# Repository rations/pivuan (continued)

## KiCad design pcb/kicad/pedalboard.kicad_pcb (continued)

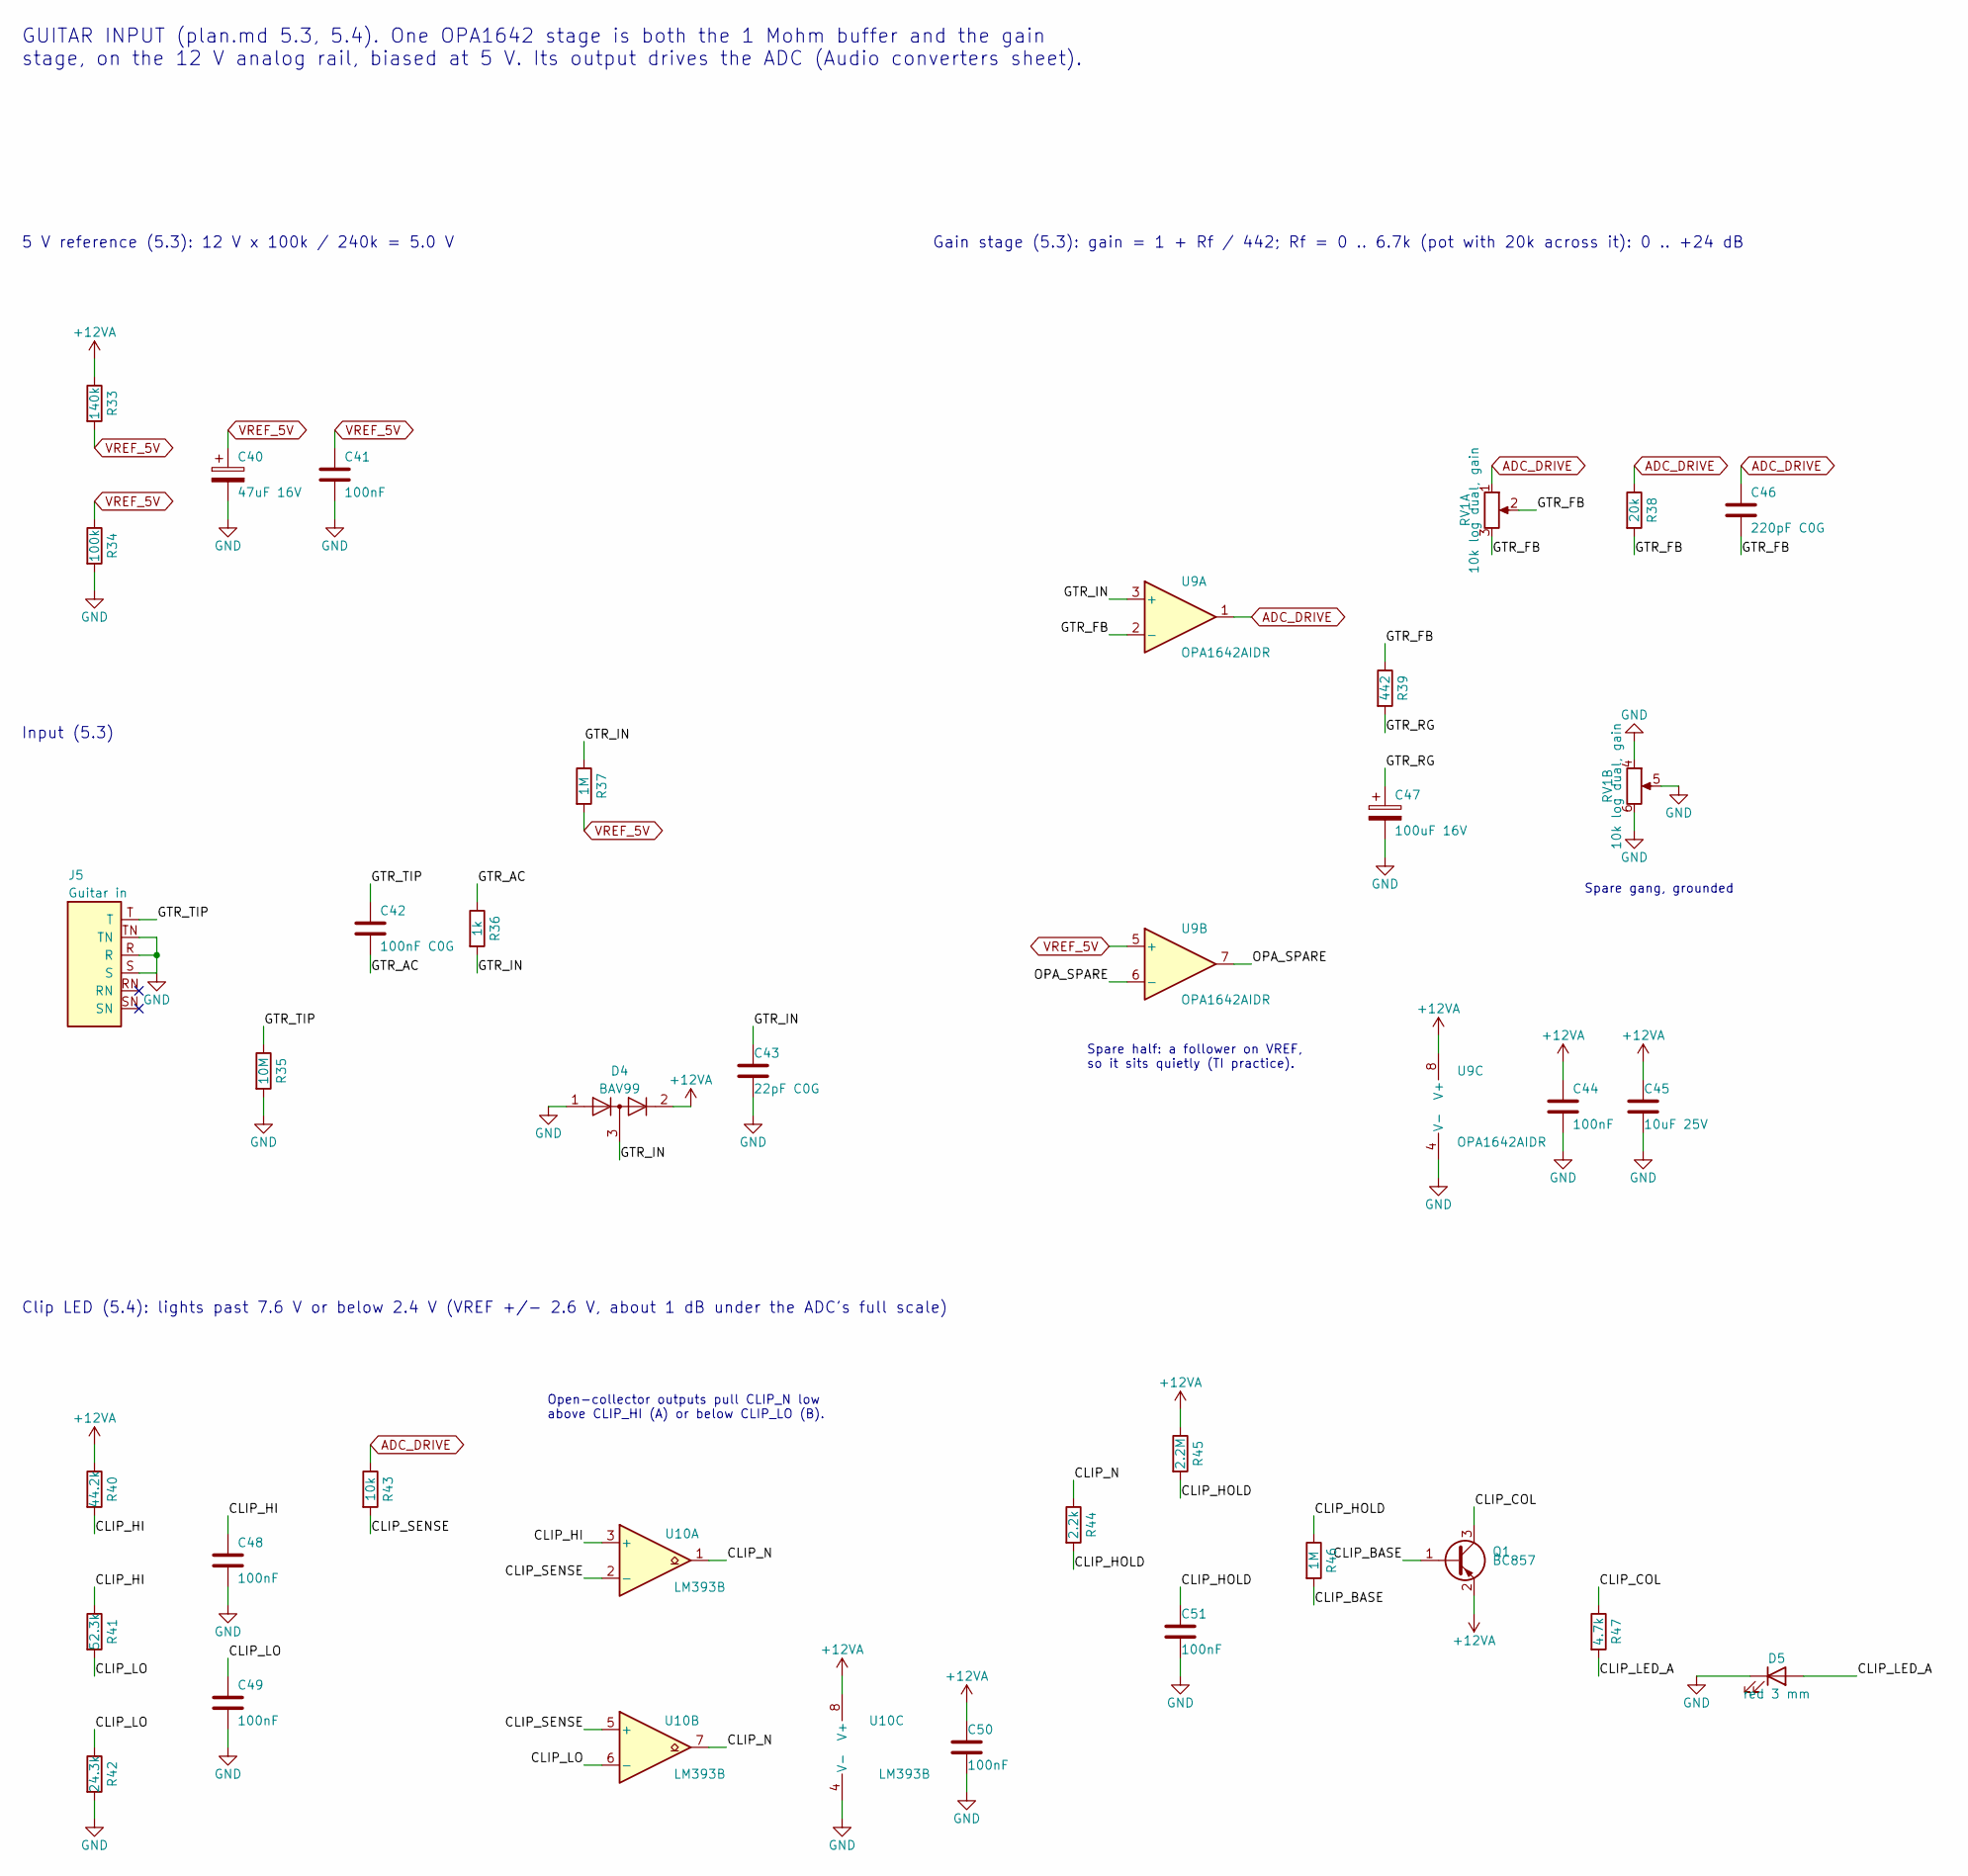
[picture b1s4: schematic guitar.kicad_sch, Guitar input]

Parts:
C40: 47uF 16V; CP_Elec_5x5.4; MPN RVT1C470M0505; LCSC C72515
C41, C44, C48, C49, C50, C51: 100nF; C_0603_1608Metric; MPN CC0603KRX7R9BB104; LCSC C14663
C42: 100nF C0G; C_1206_3216Metric; MPN GRM31C5C1H104JA01L; LCSC C97946
C43: 22pF C0G; C_0603_1608Metric; MPN CL10C220JB8NNNC; LCSC C1653
C45: 10uF 25V; C_1206_3216Metric; MPN CL31A106KBHNNNE; LCSC C13585
C46: 220pF C0G; C_0603_1608Metric; MPN GCM1885C2A221JA16D; LCSC C388907
C47: 100uF 16V; CP_Elec_6.3x5.4; MPN RVT1C101M0605; LCSC C72475
D4: BAV99; SOT-23; MPN BAV99,215; LCSC C2500
D5: red 3 mm; LED_D3.0mm_Horizontal_O1.27mm_Z6.0mm; MPN 204-10SURD/S530-A3-L; LCSC C99771
J5: Guitar in; Jack_6.35mm_Neutrik_NMJ6HCD2_Horizontal; MPN NMJ6HCD2; LCSC C368502
Q1: BC857; SOT-23; MPN BC857C,215; LCSC C8666
R33: 140k; R_0603_1608Metric; MPN RC0603FR-07140KL; LCSC C185372
R34: 100k; R_0603_1608Metric; MPN 0603WAF1003T5E; LCSC C25803
R35: 10M; R_0603_1608Metric; MPN 0603WAF1005T5E; LCSC C7250
R36: 1k; R_0603_1608Metric; MPN 0603WAF1001T5E; LCSC C21190
R37, R46: 1M; R_0603_1608Metric; MPN 0603WAF1004T5E; LCSC C22935
R38: 20k; R_0603_1608Metric; MPN 0603WAF2002T5E; LCSC C4184
R39: 442; R_0603_1608Metric; MPN 0603WAF4420T5E; LCSC C23057
R40: 44.2k; R_0603_1608Metric; MPN AT0603BRD0744K2L; LCSC C855860
R41: 52.3k; R_0603_1608Metric; MPN RS-03K5232FT; LCSC C304764
R42: 24.3k; R_0603_1608Metric; MPN RT0603BRD0724K3L; LCSC C136968
R43: 10k; R_0603_1608Metric; MPN 0603WAF1002T5E; LCSC C25804
R44: 2.2k; R_0603_1608Metric; MPN 0603WAF2201T5E; LCSC C4190
R45: 2.2M; R_0603_1608Metric; MPN 0603WAF2204T5E; LCSC C22938
R47: 4.7k; R_0603_1608Metric; MPN 0603WAF4701T5E; LCSC C23162
RV1: 10k log dual, gain; Potentiometer_Alps_RK09L_Double_Horizontal; MPN RK09L12B0A4S
U9: OPA1642AIDR; SOIC-8_3.9x4.9mm_P1.27mm; MPN OPA1642AIDR; LCSC C67640
U10: LM393B; SOIC-8_3.9x4.9mm_P1.27mm; MPN LM393BIDR

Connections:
+12VA: C44.1, C45.1, C50.1, D4.2 (A), Q1.2 (E), R33.1, R40.1, R45.1, U9.8 (V+), U10.8 (V+); also elsewhere on the board
/Guitar input/CLIP_BASE: Q1.1 (B), R46.2
/Guitar input/CLIP_COL: Q1.3 (C), R47.1
/Guitar input/CLIP_HI: C48.1, R40.2, R41.1, U10.3 (+)
/Guitar input/CLIP_HOLD: C51.1, R44.2, R45.2, R46.1
/Guitar input/CLIP_LED_A: D5.2 (A), R47.2
/Guitar input/CLIP_LO: C49.1, R41.2, R42.1, U10.6 (-)
/Guitar input/CLIP_N: R44.1, U10.1, U10.7
/Guitar input/CLIP_SENSE: R43.2, U10.2 (-), U10.5 (+)
/Guitar input/GTR_AC: C42.2, R36.1
/Guitar input/GTR_FB: C46.2, R38.2, R39.1, RV1.2, RV1.3, U9.2 (-)
/Guitar input/GTR_IN: C43.1, D4.3 (K), R36.2, R37.1, U9.3 (+)
/Guitar input/GTR_RG: C47.1, R39.2
/Guitar input/GTR_TIP: C42.1, J5.T, R35.1
/Guitar input/OPA_SPARE: U9.6 (-), U9.7
ADC_DRIVE: C46.1, R38.1, R43.1, RV1.1, U9.1; also elsewhere on the board
GND: C40.2, C41.2, C43.2, C44.2, C45.2, C47.2, C48.2, C49.2, C50.2, C51.2, D4.1 (K), D5.1 (K), J5.R, J5.S, J5.TN, R34.2, R35.2, R42.2, RV1.4, RV1.5, RV1.6, U9.4 (V-), U10.4 (V-); also elsewhere on the board
VREF_5V: C40.1, C41.1, R33.2, R34.1, R37.2, U9.5 (+); also elsewhere on the board

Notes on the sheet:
GUITAR INPUT (plan.md 5.3, 5.4). One OPA1642 stage is both the 1 Mohm buffer and the gain stage, on the 12 V analog rail, biased at 5 V. Its output drives the ADC (Audio converters sheet).
5 V reference (5.3): 12 V x 100k / 240k = 5.0 V
Input (5.3)
Gain stage (5.3): gain = 1 + Rf / 442; Rf = 0 .. 6.7k (pot with 20k across it): 0 .. +24 dB
Spare half: a follower on VREF, so it sits quietly (TI practice).
Spare gang, grounded
Clip LED (5.4): lights past 7.6 V or below 2.4 V (VREF +/- 2.6 V, about 1 dB under the ADC's full scale)
Open-collector outputs pull CLIP_N low above CLIP_HI (A) or below CLIP_LO (B).

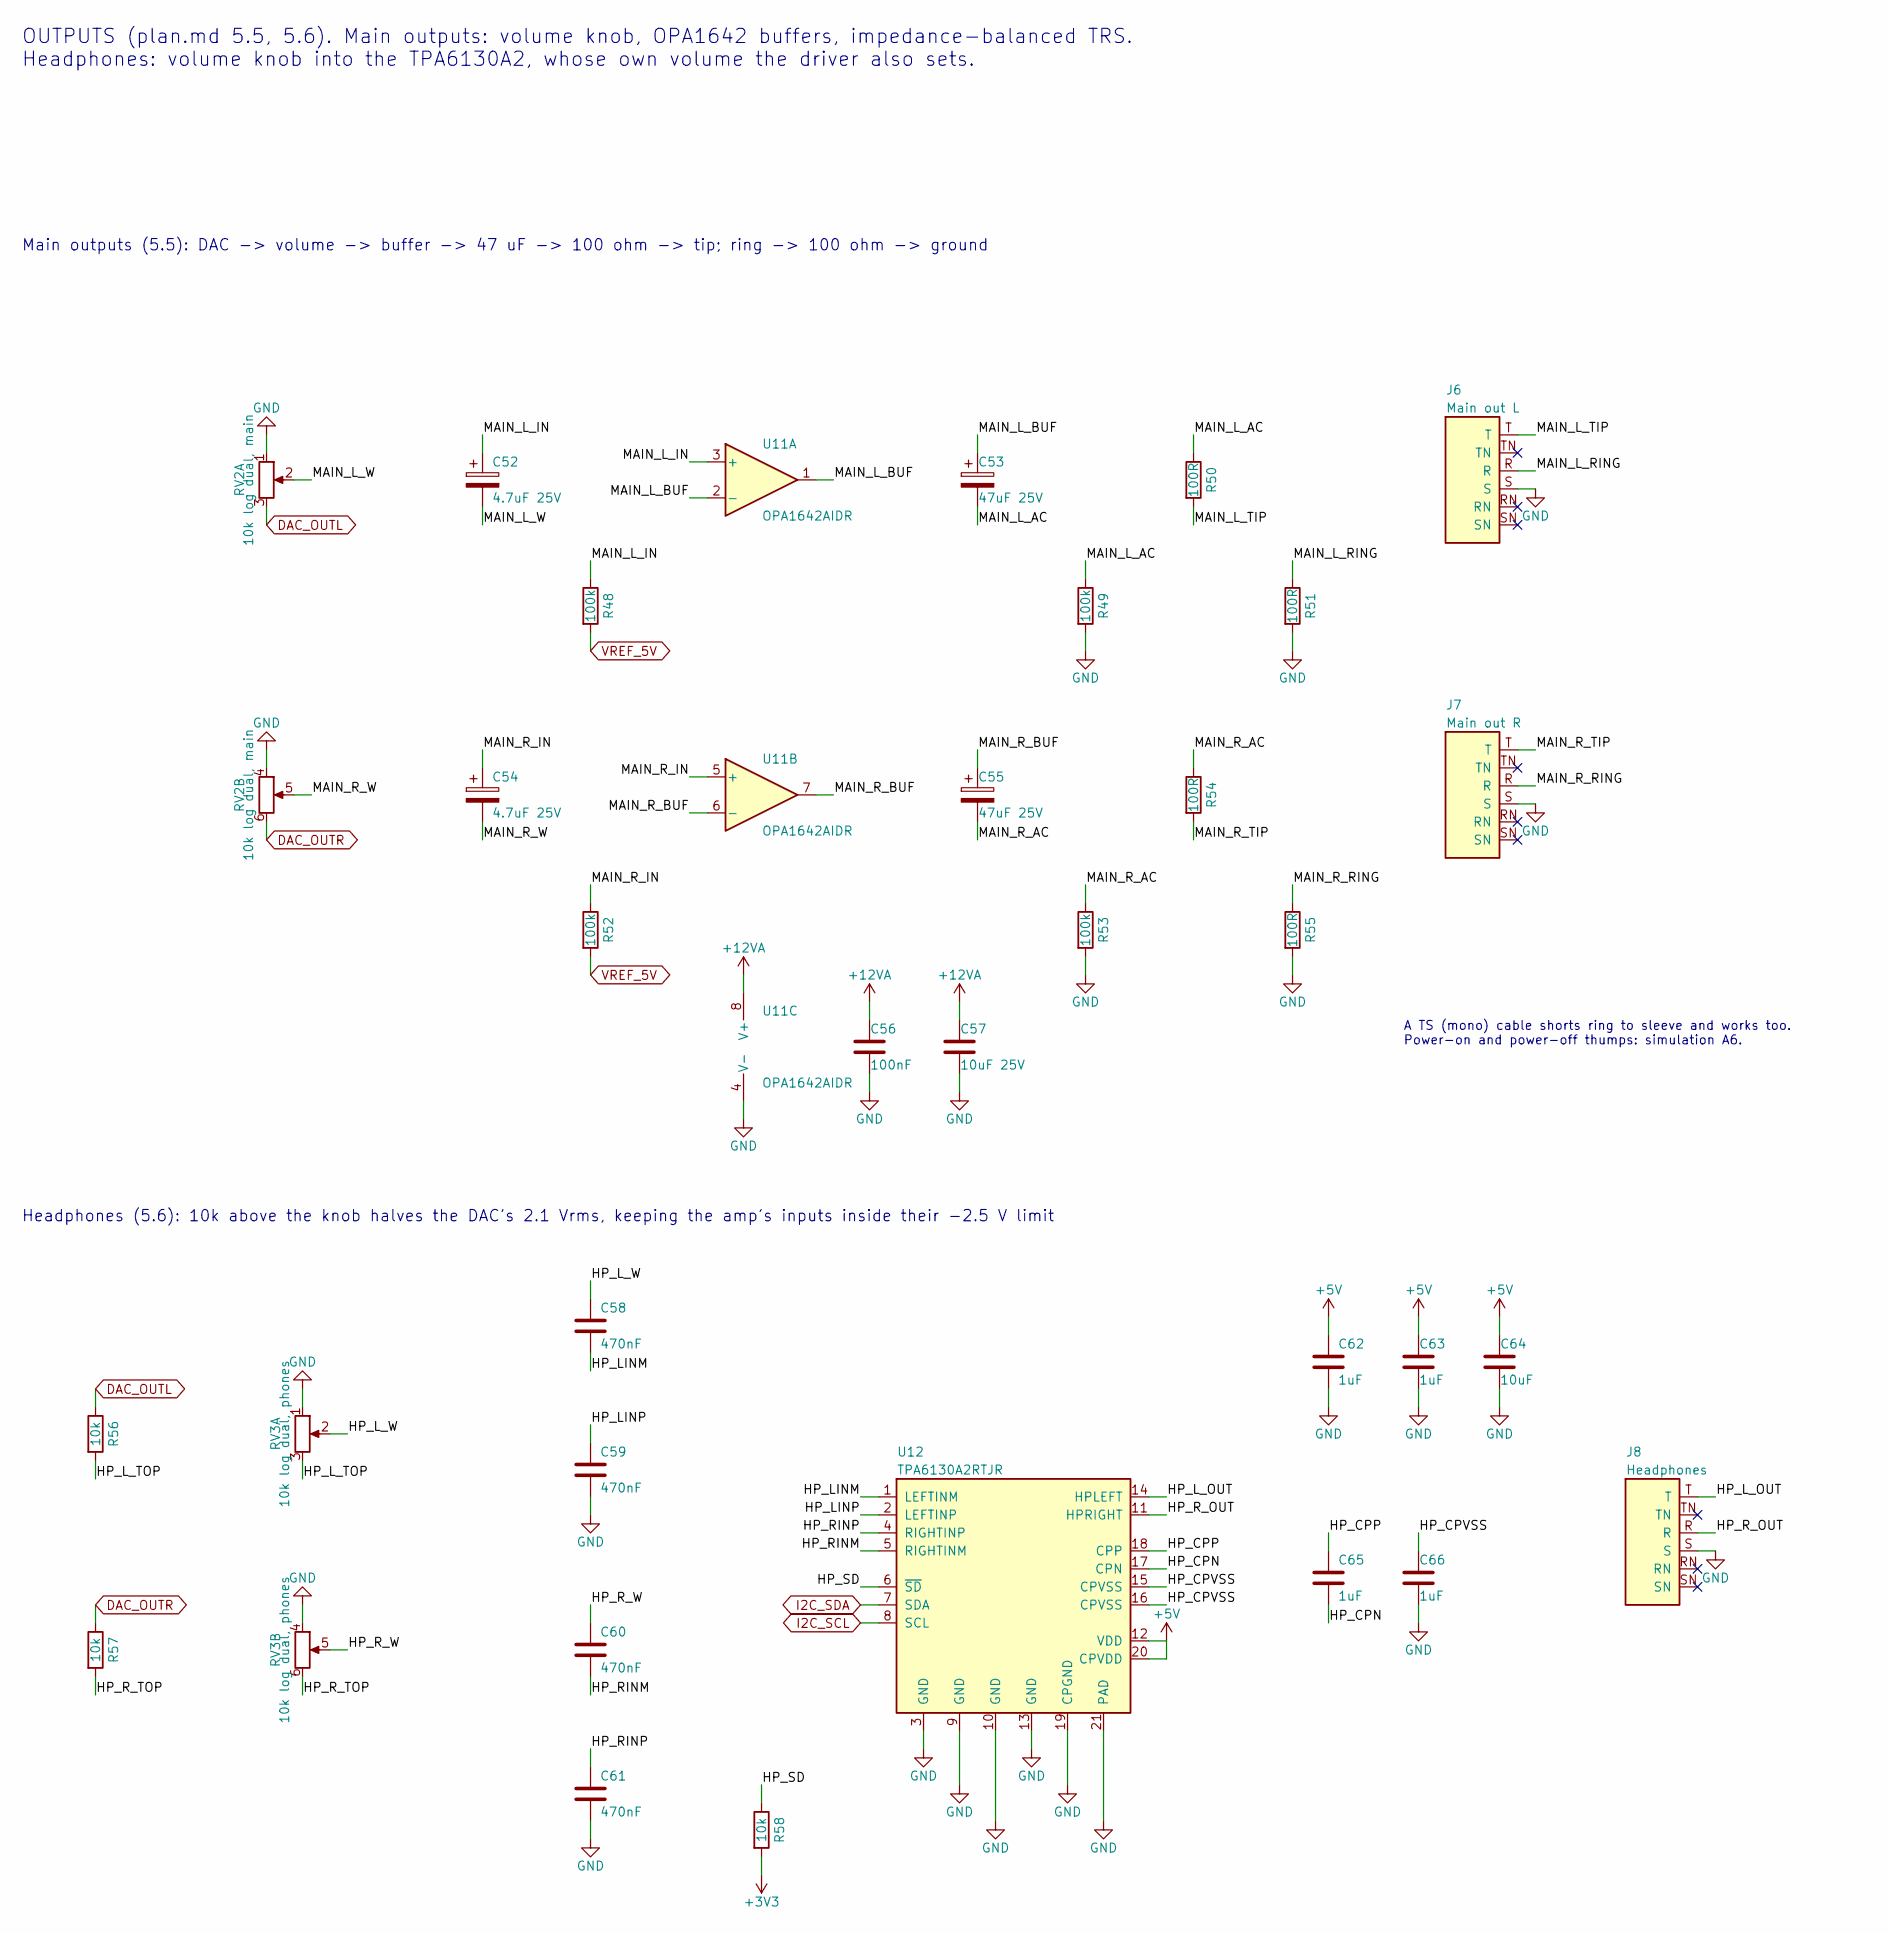
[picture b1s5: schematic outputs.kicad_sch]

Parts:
C52, C54: 4.7uF 25V; CP_Elec_4x5.4; MPN RVT1V4R7M0405; LCSC C72511
C53, C55: 47uF 25V; CP_Elec_6.3x5.4; MPN RVT1E470M0605; LCSC C72521
C56: 100nF; C_0603_1608Metric; MPN CC0603KRX7R9BB104; LCSC C14663
C57: 10uF 25V; C_1206_3216Metric; MPN CL31A106KBHNNNE; LCSC C13585
C58, C59, C60, C61: 470nF; C_0805_2012Metric; MPN CL21B474KBFNNNE; LCSC C13967
C62, C63, C65, C66: 1uF; C_0603_1608Metric; MPN CL10A105KB8NNNC; LCSC C15849
C64: 10uF; C_0805_2012Metric; MPN CL21A106KAYNNNE; LCSC C15850
J6: Main out L; Jack_6.35mm_Neutrik_NMJ6HCD2_Horizontal; MPN NMJ6HCD2; LCSC C368502
J7: Main out R; Jack_6.35mm_Neutrik_NMJ6HCD2_Horizontal; MPN NMJ6HCD2; LCSC C368502
J8: Headphones; Jack_6.35mm_Neutrik_NMJ6HCD2_Horizontal; MPN NMJ6HCD2; LCSC C368502
R48, R49, R52, R53: 100k; R_0603_1608Metric; MPN 0603WAF1003T5E; LCSC C25803
R50, R51, R54, R55: 100R; R_0603_1608Metric; MPN 0603WAF1000T5E; LCSC C22775
R56, R57, R58: 10k; R_0603_1608Metric; MPN 0603WAF1002T5E; LCSC C25804
RV2: 10k log dual, main; Potentiometer_Alps_RK09L_Double_Horizontal; MPN RK09L12B0A4S
RV3: 10k log dual, phones; Potentiometer_Alps_RK09L_Double_Horizontal; MPN RK09L12B0A4S
U11: OPA1642AIDR; SOIC-8_3.9x4.9mm_P1.27mm; MPN OPA1642AIDR; LCSC C67640
U12: TPA6130A2RTJR; QFN-20-1EP_4x4mm_P0.5mm_EP2.7x2.7mm; MPN TPA6130A2RTJR; LCSC C130046

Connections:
+3V3: R58.2; also elsewhere on the board
+5V: C62.1, C63.1, C64.1, U12.12 (VDD), U12.20 (CPVDD); also elsewhere on the board
+12VA: C56.1, C57.1, U11.8 (V+); also elsewhere on the board
/Outputs/HP_CPN: C65.2, U12.17 (CPN)
/Outputs/HP_CPP: C65.1, U12.18 (CPP)
/Outputs/HP_CPVSS: C66.1, U12.15 (CPVSS), U12.16 (CPVSS)
/Outputs/HP_LINM: C58.2, U12.1 (LEFTINM)
/Outputs/HP_LINP: C59.1, U12.2 (LEFTINP)
/Outputs/HP_L_OUT: J8.T, U12.14 (HPLEFT)
/Outputs/HP_L_TOP: R56.2, RV3.3
/Outputs/HP_L_W: C58.1, RV3.2
/Outputs/HP_RINM: C60.2, U12.5 (RIGHTINM)
/Outputs/HP_RINP: C61.1, U12.4 (RIGHTINP)
/Outputs/HP_R_OUT: J8.R, U12.11 (HPRIGHT)
/Outputs/HP_R_TOP: R57.2, RV3.6
/Outputs/HP_R_W: C60.1, RV3.5
/Outputs/HP_SD: R58.1, U12.6 (~SD)
/Outputs/MAIN_L_AC: C53.2, R49.1, R50.1
/Outputs/MAIN_L_BUF: C53.1, U11.1, U11.2 (-)
/Outputs/MAIN_L_IN: C52.1, R48.1, U11.3 (+)
/Outputs/MAIN_L_RING: J6.R, R51.1
/Outputs/MAIN_L_TIP: J6.T, R50.2
/Outputs/MAIN_L_W: C52.2, RV2.2
/Outputs/MAIN_R_AC: C55.2, R53.1, R54.1
/Outputs/MAIN_R_BUF: C55.1, U11.6 (-), U11.7
/Outputs/MAIN_R_IN: C54.1, R52.1, U11.5 (+)
/Outputs/MAIN_R_RING: J7.R, R55.1
/Outputs/MAIN_R_TIP: J7.T, R54.2
/Outputs/MAIN_R_W: C54.2, RV2.5
DAC_OUTL: R56.1, RV2.3; also elsewhere on the board
DAC_OUTR: R57.1, RV2.6; also elsewhere on the board
GND: C56.2, C57.2, C59.2, C61.2, C62.2, C63.2, C64.2, C66.2, J6.S, J7.S, J8.S, R49.2, R51.2, R53.2, R55.2, RV2.1, RV2.4, RV3.1, RV3.4, U11.4 (V-), U12.3 (GND), U12.9 (GND), U12.10 (GND), U12.13 (GND), U12.19 (CPGND), U12.21 (PAD); also elsewhere on the board
I2C_SCL: U12.8 (SCL); also elsewhere on the board
I2C_SDA: U12.7 (SDA); also elsewhere on the board
VREF_5V: R48.2, R52.2; also elsewhere on the board

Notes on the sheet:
OUTPUTS (plan.md 5.5, 5.6). Main outputs: volume knob, OPA1642 buffers, impedance-balanced TRS. Headphones: volume knob into the TPA6130A2, whose own volume the driver also sets.
Main outputs (5.5): DAC -> volume -> buffer -> 47 uF -> 100 ohm -> tip; ring -> 100 ohm -> ground
A TS (mono) cable shorts ring to sleeve and works too. Power-on and power-off thumps: simulation A6.
Headphones (5.6): 10k above the knob halves the DAC's 2.1 Vrms, keeping the amp's inputs inside their -2.5 V limit

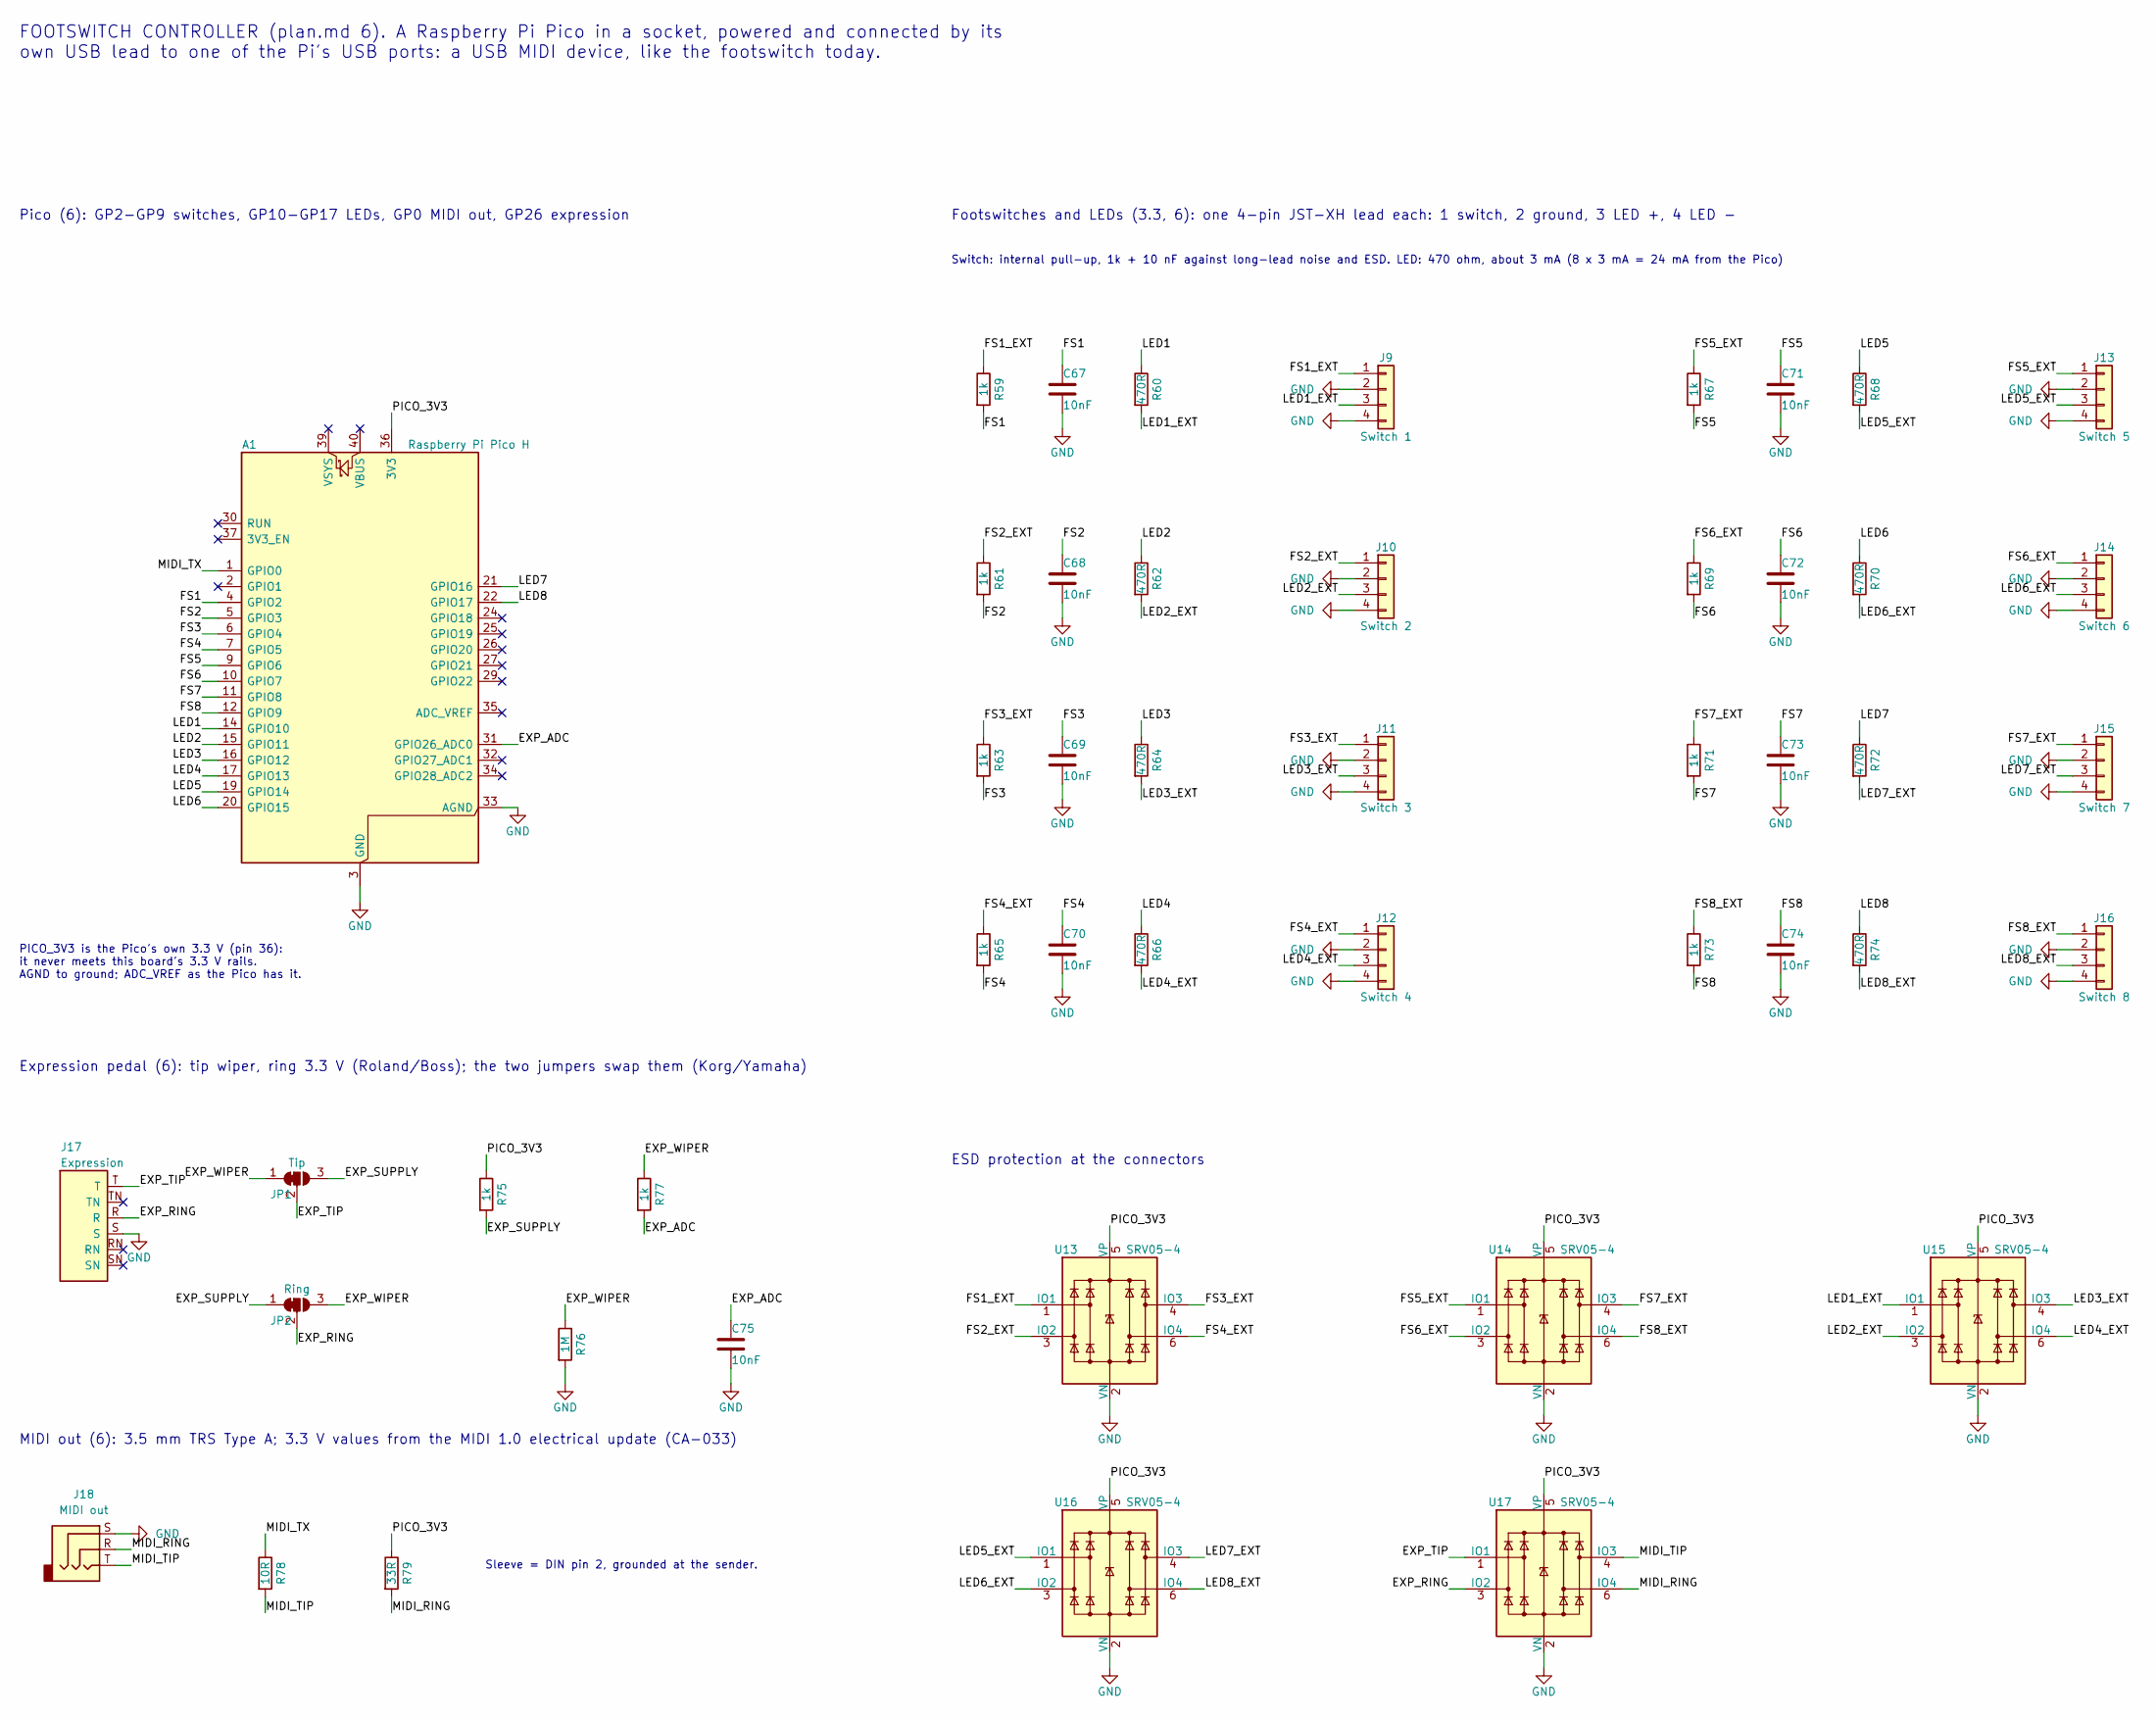
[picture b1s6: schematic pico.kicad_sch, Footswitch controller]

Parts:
A1: Raspberry Pi Pico H; RaspberryPi_Pico_Common_THT; MPN Pico H
C67, C68, C69, C70, C71, C72, C73, C74, C75: 10nF; C_0603_1608Metric; MPN 0603B103K500NT; LCSC C57112
J9: Switch 1; JST_XH_B4B-XH-A_1x04_P2.50mm_Vertical; MPN B4B-XH-A(LF)(SN); LCSC C144395
J10: Switch 2; JST_XH_B4B-XH-A_1x04_P2.50mm_Vertical; MPN B4B-XH-A(LF)(SN); LCSC C144395
J11: Switch 3; JST_XH_B4B-XH-A_1x04_P2.50mm_Vertical; MPN B4B-XH-A(LF)(SN); LCSC C144395
J12: Switch 4; JST_XH_B4B-XH-A_1x04_P2.50mm_Vertical; MPN B4B-XH-A(LF)(SN); LCSC C144395
J13: Switch 5; JST_XH_B4B-XH-A_1x04_P2.50mm_Vertical; MPN B4B-XH-A(LF)(SN); LCSC C144395
J14: Switch 6; JST_XH_B4B-XH-A_1x04_P2.50mm_Vertical; MPN B4B-XH-A(LF)(SN); LCSC C144395
J15: Switch 7; JST_XH_B4B-XH-A_1x04_P2.50mm_Vertical; MPN B4B-XH-A(LF)(SN); LCSC C144395
J16: Switch 8; JST_XH_B4B-XH-A_1x04_P2.50mm_Vertical; MPN B4B-XH-A(LF)(SN); LCSC C144395
J17: Expression; Jack_6.35mm_Neutrik_NMJ6HCD2_Horizontal; MPN NMJ6HCD2; LCSC C368502
J18: MIDI out; Jack_3.5mm_SameSky_SJ1-3543_Horizontal; MPN SJ1-3543
JP1: Tip; SolderJumper-3_P1.3mm_Bridged12_RoundedPad1.0x1.5mm
JP2: Ring; SolderJumper-3_P1.3mm_Bridged12_RoundedPad1.0x1.5mm
R59, R61, R63, R65, R67, R69, R71, R73, R75, R77: 1k; R_0603_1608Metric; MPN 0603WAF1001T5E; LCSC C21190
R60, R62, R64, R66, R68, R70, R72, R74: 470R; R_0603_1608Metric; MPN 0603WAF4700T5E; LCSC C23179
R76: 1M; R_0603_1608Metric; MPN 0603WAF1004T5E; LCSC C22935
R78: 10R; R_0603_1608Metric; MPN 0603WAF100JT5E; LCSC C22859
R79: 33R; R_1210_3225Metric; MPN RC1210FR-0733RL; LCSC C723447
U13, U14, U15, U16, U17: SRV05-4; SOT-23-6; MPN SRV05-4; LCSC C384887

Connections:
/Footswitch controller/EXP_ADC: A1.31 (GPIO26_ADC0), C75.1, R77.2
/Footswitch controller/EXP_RING: J17.R, JP2.2 (C), U17.3 (IO2)
/Footswitch controller/EXP_SUPPLY: JP1.3 (B), JP2.1 (A), R75.2
/Footswitch controller/EXP_TIP: J17.T, JP1.2 (C), U17.1 (IO1)
/Footswitch controller/EXP_WIPER: JP1.1 (A), JP2.3 (B), R76.1, R77.1
/Footswitch controller/FS1: A1.4 (GPIO2), C67.1, R59.2
/Footswitch controller/FS1_EXT: J9.1, R59.1, U13.1 (IO1)
/Footswitch controller/FS2: A1.5 (GPIO3), C68.1, R61.2
/Footswitch controller/FS2_EXT: J10.1, R61.1, U13.3 (IO2)
/Footswitch controller/FS3: A1.6 (GPIO4), C69.1, R63.2
/Footswitch controller/FS3_EXT: J11.1, R63.1, U13.4 (IO3)
/Footswitch controller/FS4: A1.7 (GPIO5), C70.1, R65.2
/Footswitch controller/FS4_EXT: J12.1, R65.1, U13.6 (IO4)
/Footswitch controller/FS5: A1.9 (GPIO6), C71.1, R67.2
/Footswitch controller/FS5_EXT: J13.1, R67.1, U14.1 (IO1)
/Footswitch controller/FS6: A1.10 (GPIO7), C72.1, R69.2
/Footswitch controller/FS6_EXT: J14.1, R69.1, U14.3 (IO2)
/Footswitch controller/FS7: A1.11 (GPIO8), C73.1, R71.2
/Footswitch controller/FS7_EXT: J15.1, R71.1, U14.4 (IO3)
/Footswitch controller/FS8: A1.12 (GPIO9), C74.1, R73.2
/Footswitch controller/FS8_EXT: J16.1, R73.1, U14.6 (IO4)
/Footswitch controller/LED1: A1.14 (GPIO10), R60.1
/Footswitch controller/LED1_EXT: J9.3, R60.2, U15.1 (IO1)
/Footswitch controller/LED2: A1.15 (GPIO11), R62.1
/Footswitch controller/LED2_EXT: J10.3, R62.2, U15.3 (IO2)
/Footswitch controller/LED3: A1.16 (GPIO12), R64.1
/Footswitch controller/LED3_EXT: J11.3, R64.2, U15.4 (IO3)
/Footswitch controller/LED4: A1.17 (GPIO13), R66.1
/Footswitch controller/LED4_EXT: J12.3, R66.2, U15.6 (IO4)
/Footswitch controller/LED5: A1.19 (GPIO14), R68.1
/Footswitch controller/LED5_EXT: J13.3, R68.2, U16.1 (IO1)
/Footswitch controller/LED6: A1.20 (GPIO15), R70.1
/Footswitch controller/LED6_EXT: J14.3, R70.2, U16.3 (IO2)
/Footswitch controller/LED7: A1.21 (GPIO16), R72.1
/Footswitch controller/LED7_EXT: J15.3, R72.2, U16.4 (IO3)
/Footswitch controller/LED8: A1.22 (GPIO17), R74.1
/Footswitch controller/LED8_EXT: J16.3, R74.2, U16.6 (IO4)
/Footswitch controller/MIDI_RING: J18.R, R79.2, U17.6 (IO4)
/Footswitch controller/MIDI_TIP: J18.T, R78.2, U17.4 (IO3)
/Footswitch controller/MIDI_TX: A1.1 (GPIO0), R78.1
/Footswitch controller/PICO_3V3: A1.36 (3V3), R75.1, R79.1, U13.5 (VP), U14.5 (VP), U15.5 (VP), U16.5 (VP), U17.5 (VP)
GND: A1.3 (GND), A1.8 (GND), A1.13 (GND), A1.18 (GND), A1.23 (GND), A1.28 (GND), A1.33 (AGND), A1.38 (GND), C67.2, C68.2, C69.2, C70.2, C71.2, C72.2, C73.2, C74.2, C75.2, J9.2, J9.4, J10.2, J10.4, J11.2, J11.4, J12.2, J12.4, J13.2, J13.4, J14.2, J14.4, J15.2, J15.4, J16.2, J16.4, J17.S, J18.S, R76.2, U13.2 (VN), U14.2 (VN), U15.2 (VN), U16.2 (VN), U17.2 (VN); also elsewhere on the board

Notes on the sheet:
FOOTSWITCH CONTROLLER (plan.md 6). A Raspberry Pi Pico in a socket, powered and connected by its own USB lead to one of the Pi's USB ports: a USB MIDI device, like the footswitch today.
Pico (6): GP2-GP9 switches, GP10-GP17 LEDs, GP0 MIDI out, GP26 expression
PICO_3V3 is the Pico's own 3.3 V (pin 36): it never meets this board's 3.3 V rails. AGND to ground; ADC_VREF as the Pico has it.
Footswitches and LEDs (3.3, 6): one 4-pin JST-XH lead each: 1 switch, 2 ground, 3 LED +, 4 LED -
Switch: internal pull-up, 1k + 10 nF against long-lead noise and ESD. LED: 470 ohm, about 3 mA (8 x 3 mA = 24 mA from the Pico)
ESD protection at the connectors
Expression pedal (6): tip wiper, ring 3.3 V (Roland/Boss); the two jumpers swap them (Korg/Yamaha)
MIDI out (6): 3.5 mm TRS Type A; 3.3 V values from the MIDI 1.0 electrical update (CA-033)
Sleeve = DIN pin 2, grounded at the sender.

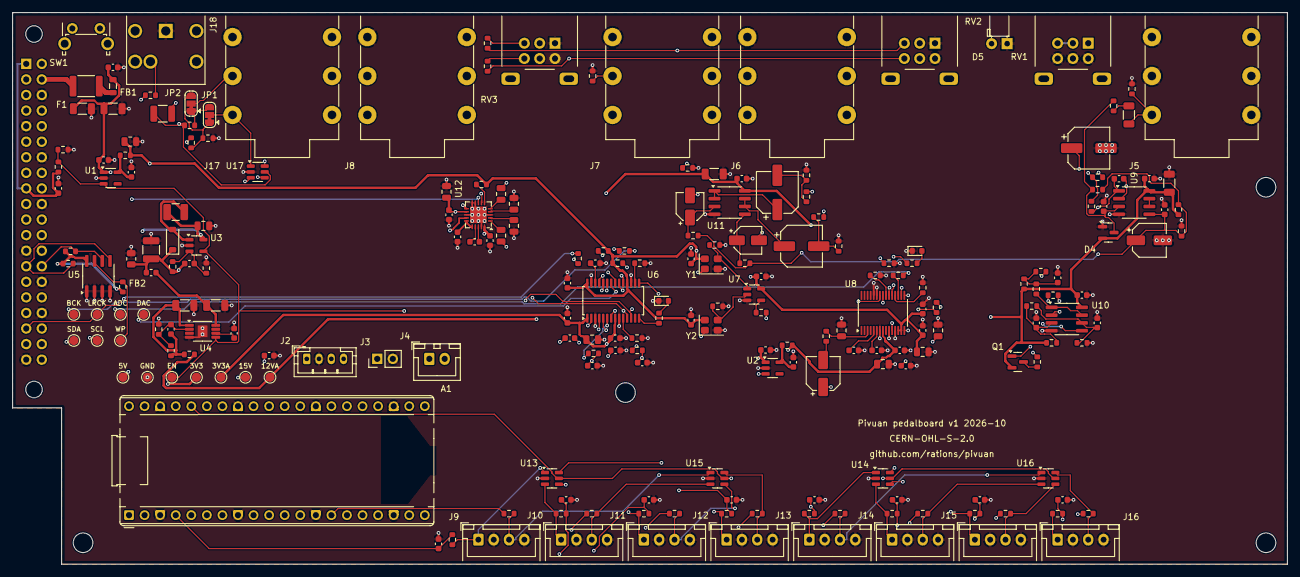
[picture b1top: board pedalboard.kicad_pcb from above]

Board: 4 copper layers, 208.0 x 90.0 mm, 228 parts (1 on the bottom side), 146 nets.

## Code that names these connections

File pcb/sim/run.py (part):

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
    # Response with a pickup and lead, against the same pickup into an ideal 1 Mohm input; and
    # the same with other values of the RF filter capacitor at the op-amp pin.
    rf_cap = [r for r in STAGE if PARTS[r].lib == "Device:C" and set(PARTS[r].pins.values()) == {"GTR_IN", "0"}][0]
    series = []
    for cval in [PARTS[rf_cap].value] + [v for v in ("100pF", "47pF", "22pF", "10pF")
                                          if v != PARTS[rf_cap].value.split()[0]]:
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# --- Outputs: plan 5.5 and 5.6, from the DAC's output pins --------------------------------

OUTPUTS = [r for r in kinet.on_sheet(PARTS, "Outputs") if r != "U12" and not
           set(PARTS[r].pins.values()) & {"P5V", "HP_CPP", "HP_CPN", "HP_CPVSS", "HP_SD"}]
DAC_NET = [r for r in kinet.touching(PARTS, kinet.on_sheet(PARTS, "Audio converters and clocks"),
                                     ["DAC_OUTL_RAW", "DAC_OUTR_RAW"]) if not r.startswith("U")]
# The 5 V reference: the divider and its capacitors (guitar sheet).
VREF_NET = [r for r in GUITAR if set(PARTS[r].pins.values()) <= {"VREF_5V", "P12VA", "0"} and r[0] in "RC"]
# The TPA6130A2 has no SPICE model. Its inputs are each half of its differential input
# impedance, to an internal point at AC ground; 37 kohm is the least, at its highest gains
# (datasheet 9.2.2.1).
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

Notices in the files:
pcb/kicad/guitar.kicad_sch:
CERN-OHL-S-2.0
